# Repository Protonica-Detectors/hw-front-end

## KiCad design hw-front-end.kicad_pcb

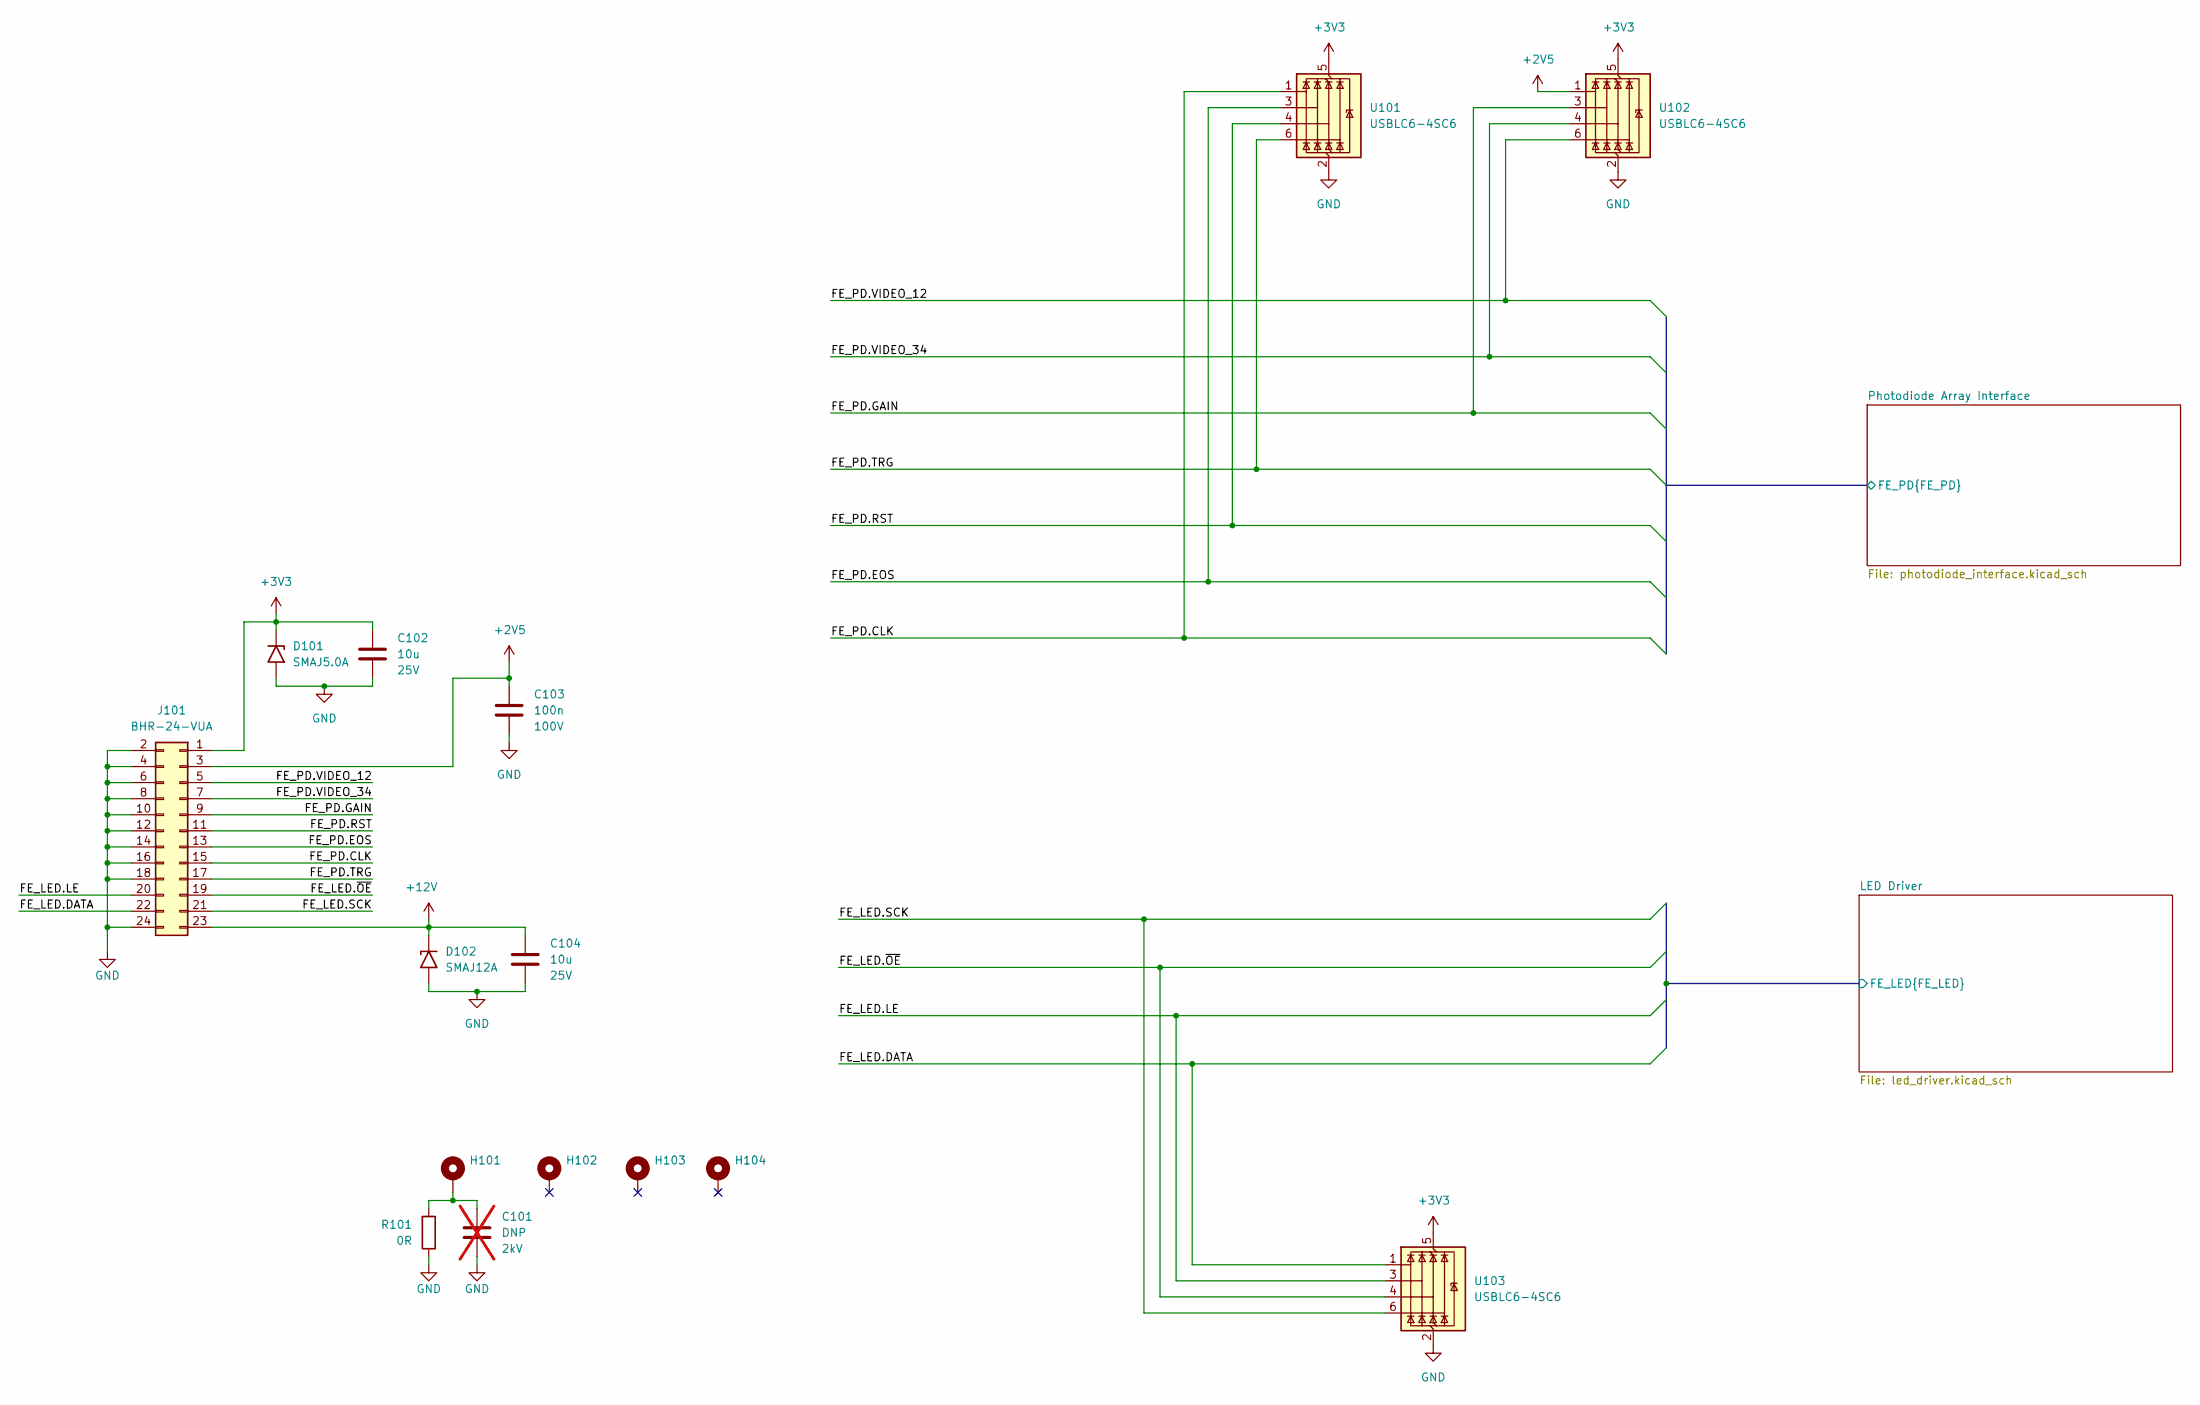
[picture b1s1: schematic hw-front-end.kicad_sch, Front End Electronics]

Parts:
C101: DNP; C_1206_3216Metric_Pad1.33x1.80mm_HandSolder; Voltage 2kV; not fitted
C102, C104: 10u; C_1206_3216Metric_Pad1.33x1.80mm_HandSolder; Voltage 25V; MPN GRM31CR71E106KA12L
C103: 100n; C_0805_2012Metric_Pad1.18x1.45mm_HandSolder; Voltage 100V; MPN GCM21BR72A104KA37L
D101: SMAJ5.0A; D_SMA; MPN SMAJ5.0A
D102: SMAJ12A; D_SMA; MPN SMAJ12A
H101, H102, H103, H104: MountingHole_Pad; MountingHole_3.2mm_M3_DIN965_Pad_TopBottom
J101: BHR-24-VUA; IDC-Header_2x12_P2.54mm_Vertical; MPN BHR-24-VUA
R101: 0R; R_0805_2012Metric_Pad1.20x1.40mm_HandSolder; MPN CRCW08050000Z0EA
U101, U102, U103: USBLC6-4SC6; SOT-23-6; MPN USBLC6-4SC6

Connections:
+2V5: C103.1, J101.3, U102.1 (I/O1); also elsewhere on the board
+3V3: C102.1, D101.1 (A1), J101.1, U101.5 (VBUS), U102.5 (VBUS), U103.5 (VBUS); also elsewhere on the board
+12V: C104.1, D102.1 (A1), J101.23; also elsewhere on the board
/LED Driver/FE_LED.DATA: J101.22, U103.1 (I/O1); also elsewhere on the board
/LED Driver/FE_LED.LE: J101.20, U103.3 (I/O2); also elsewhere on the board
/LED Driver/FE_LED.SCK: J101.21, U103.6 (I/O4); also elsewhere on the board
/LED Driver/FE_LED.~OE: J101.19, U103.4 (I/O3); also elsewhere on the board
/Photodiode Array Interface/FE_PD.CLK: J101.15, U101.1 (I/O1); also elsewhere on the board
/Photodiode Array Interface/FE_PD.EOS: J101.13, U101.3 (I/O2); also elsewhere on the board
/Photodiode Array Interface/FE_PD.GAIN: J101.9, U102.3 (I/O2); also elsewhere on the board
/Photodiode Array Interface/FE_PD.RST: J101.11, U101.4 (I/O3); also elsewhere on the board
/Photodiode Array Interface/FE_PD.TRG: J101.17, U101.6 (I/O4); also elsewhere on the board
/Photodiode Array Interface/FE_PD.VIDEO_12: J101.5, U102.6 (I/O4); also elsewhere on the board
/Photodiode Array Interface/FE_PD.VIDEO_34: J101.7, U102.4 (I/O3); also elsewhere on the board
GND: C101.2, C102.2, C103.2, C104.2, D101.2 (A2), D102.2 (A2), J101.2, J101.4, J101.6, J101.8, J101.10, J101.12, J101.14, J101.16, J101.18, J101.24, R101.1, U101.2 (GND), U102.2 (GND), U103.2 (GND); also elsewhere on the board
unnamed: C101.1, H101.1 (1_1), R101.2

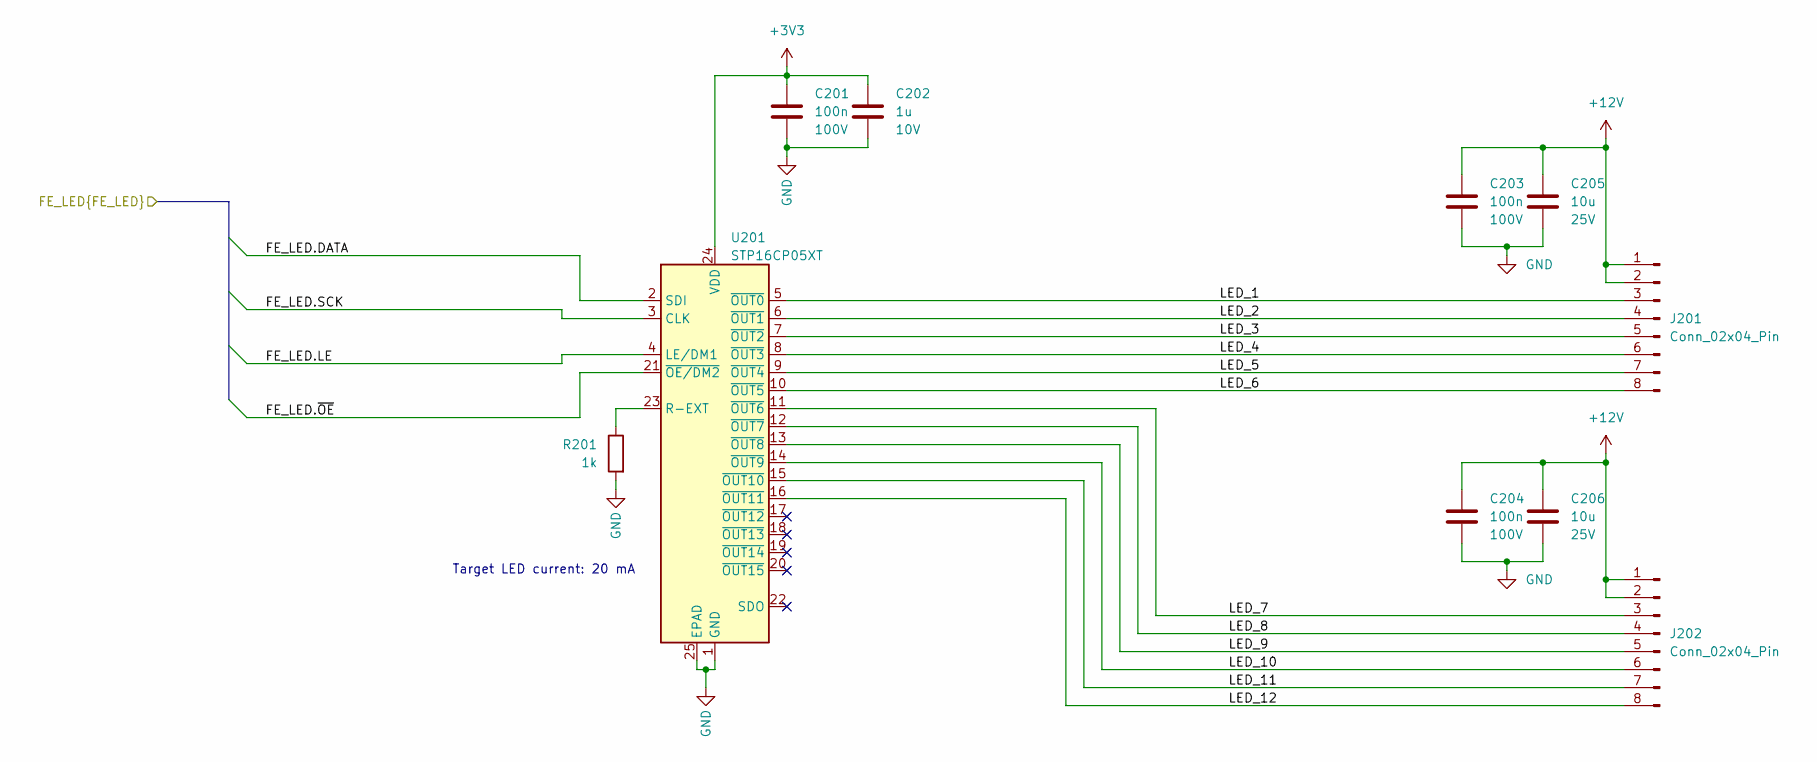
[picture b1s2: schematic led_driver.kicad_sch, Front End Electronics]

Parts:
C201, C203, C204: 100n; C_0805_2012Metric_Pad1.18x1.45mm_HandSolder; Voltage 100V; MPN GCM21BR72A104KA37L
C202: 1u; C_0805_2012Metric_Pad1.18x1.45mm_HandSolder; Voltage 10V; MPN GRM21BR71A105KA01L
C205, C206: 10u; C_1206_3216Metric_Pad1.33x1.80mm_HandSolder; Voltage 25V; MPN GRM31CR71E106KA12L
J201, J202: Conn_02x04_Pin; IDC-Header_2x04_P2.54mm_Vertical; MPN BHR-08-VUA
R201: 1k; R_0805_2012Metric_Pad1.20x1.40mm_HandSolder; MPN CRCW08051K00FKEA
U201: STP16CP05XT; HTSSOP-24-1EP_4.4x7.8mm_P0.65mm_EP3.2x5mm; MPN STP16CP05XTTR

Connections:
+3V3: C201.1, C202.1, U201.24 (VDD); also elsewhere on the board
+12V: C203.1, C204.1, C205.1, C206.1, J201.1, J201.2, J202.1, J202.2; also elsewhere on the board
/LED Driver/FE_LED.DATA: U201.2 (SDI); also elsewhere on the board
/LED Driver/FE_LED.LE: U201.4 (LE/DM1); also elsewhere on the board
/LED Driver/FE_LED.SCK: U201.3 (CLK); also elsewhere on the board
/LED Driver/FE_LED.~OE: U201.21 (~OE/DM2); also elsewhere on the board
/LED Driver/LED_1: J201.3, U201.5 (~OUT0)
/LED Driver/LED_2: J201.4, U201.6 (~OUT1)
/LED Driver/LED_3: J201.5, U201.7 (~OUT2)
/LED Driver/LED_4: J201.6, U201.8 (~OUT3)
/LED Driver/LED_5: J201.7, U201.9 (~OUT4)
/LED Driver/LED_6: J201.8, U201.10 (~OUT5)
/LED Driver/LED_7: J202.3, U201.11 (~OUT6)
/LED Driver/LED_8: J202.4, U201.12 (~OUT7)
/LED Driver/LED_9: J202.5, U201.13 (~OUT8)
/LED Driver/LED_10: J202.6, U201.14 (~OUT9)
/LED Driver/LED_11: J202.7, U201.15 (~OUT10)
/LED Driver/LED_12: J202.8, U201.16 (~OUT11)
GND: C201.2, C202.2, C203.2, C204.2, C205.2, C206.2, R201.2, U201.1 (GND), U201.25 (EPAD); also elsewhere on the board
unnamed: R201.1, U201.23 (R-EXT)

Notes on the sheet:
Target LED current: 20 mA

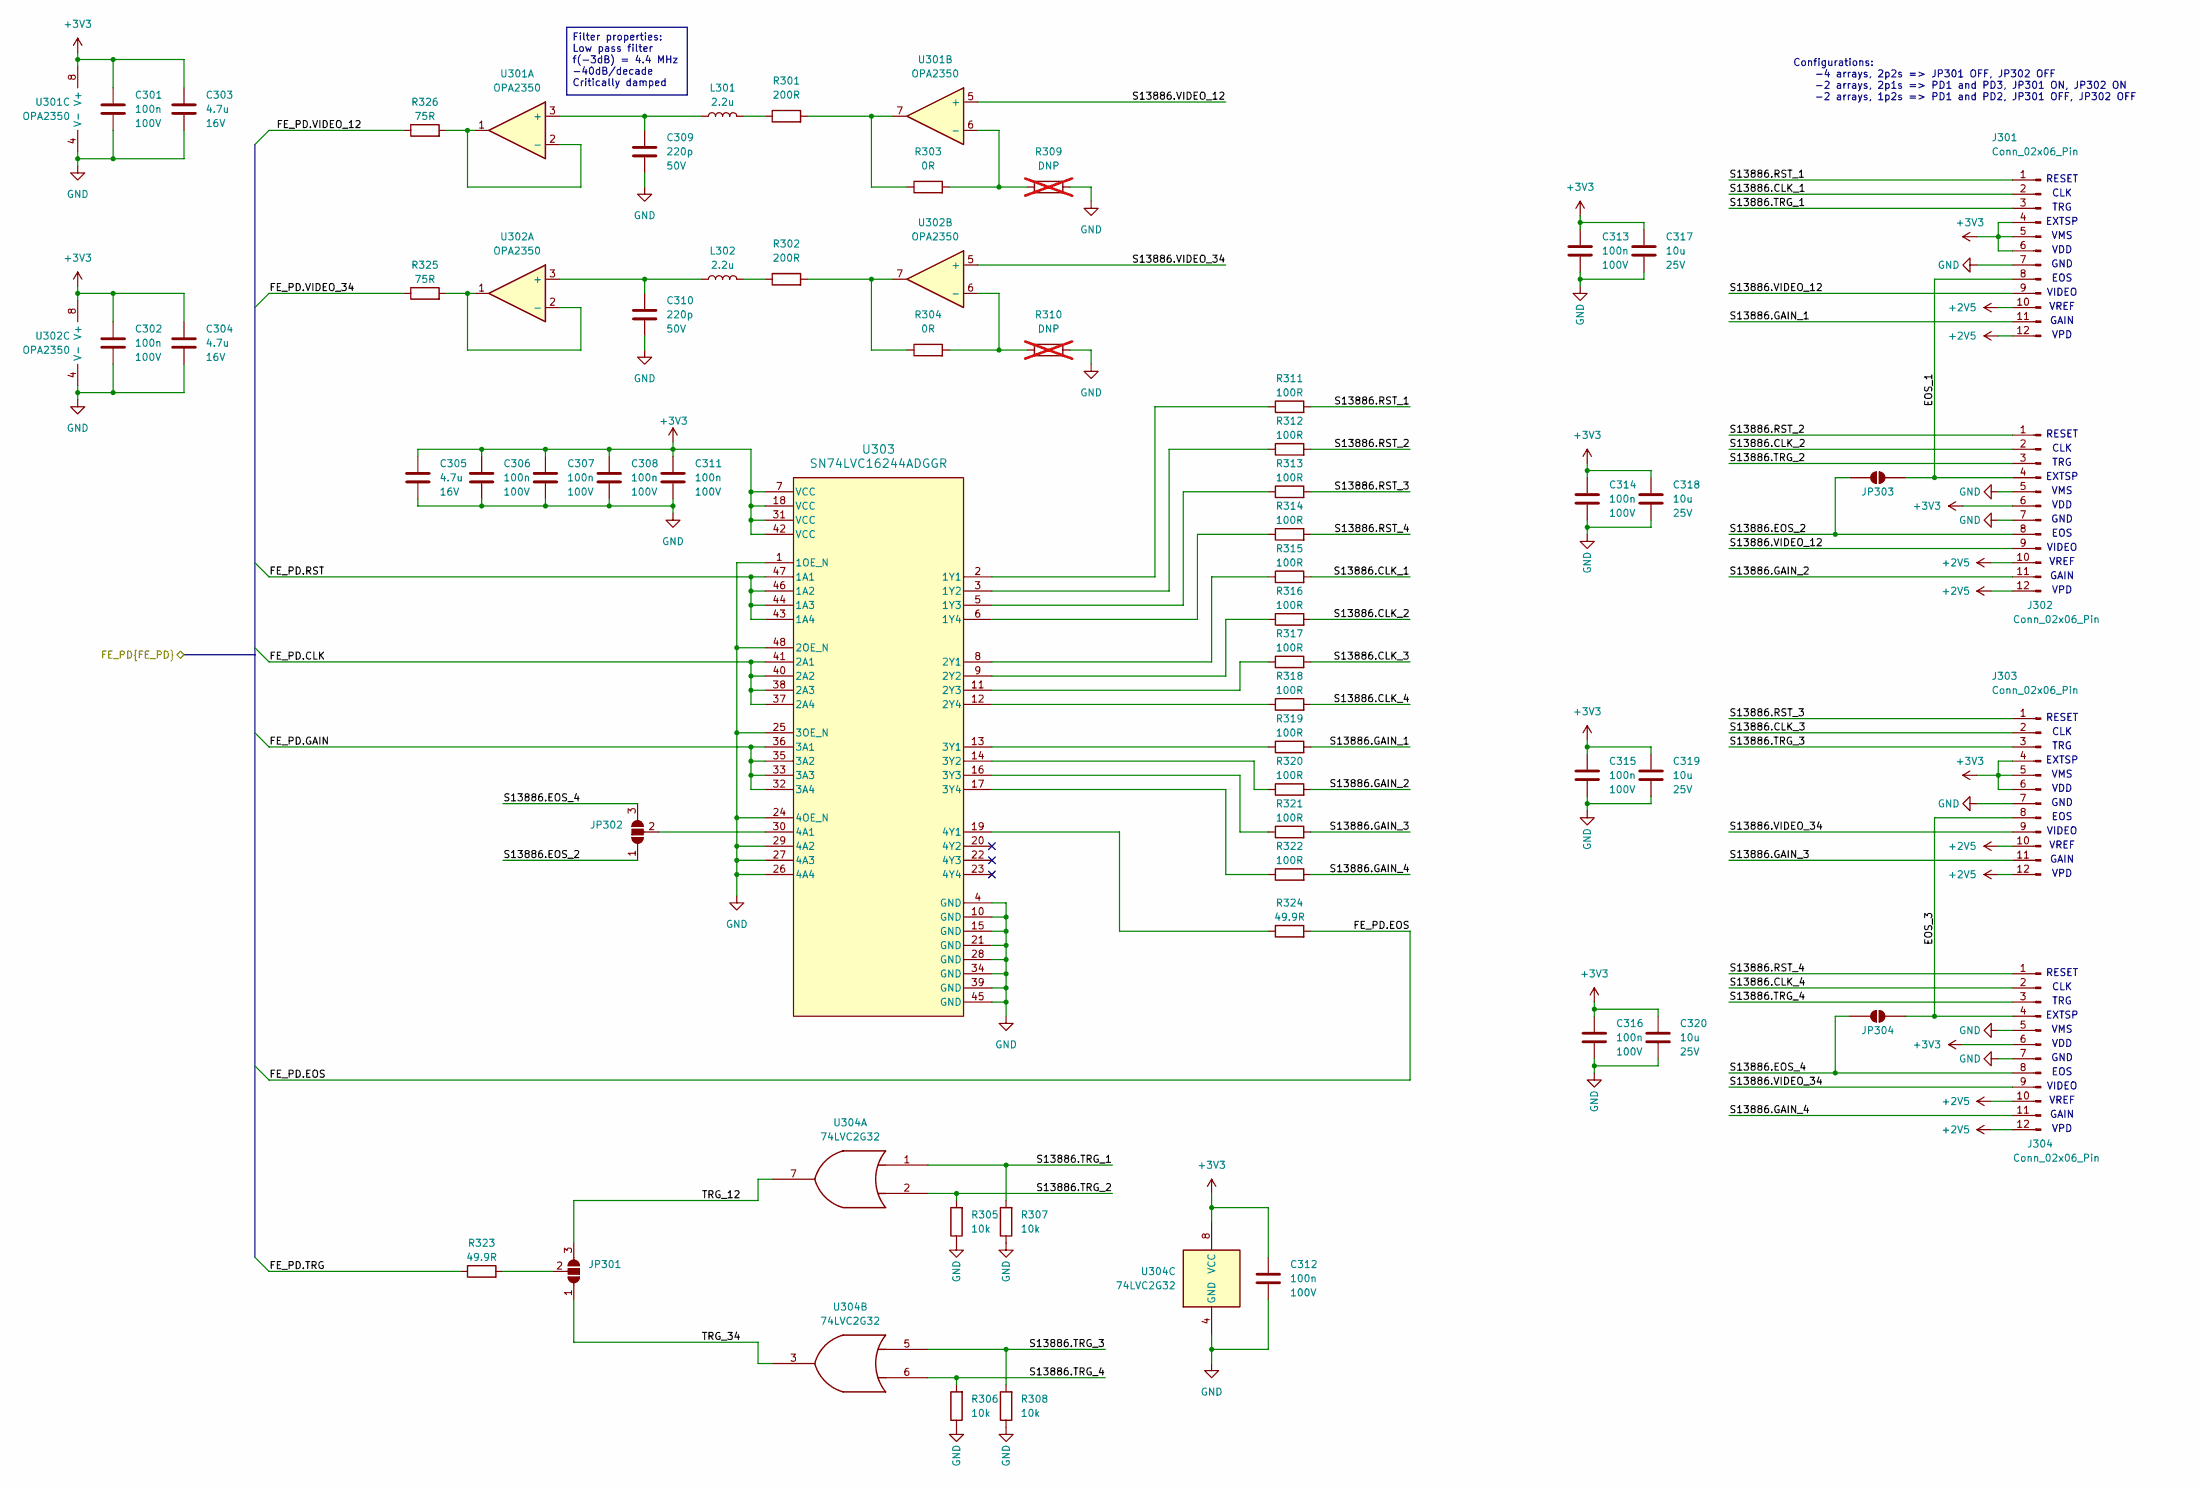
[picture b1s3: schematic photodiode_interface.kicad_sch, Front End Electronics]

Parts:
C301, C302, C306, C307, C308, C311, C312, C313, C314, C315, C316: 100n; C_0805_2012Metric_Pad1.18x1.45mm_HandSolder; Voltage 100V; MPN GCM21BR72A104KA37L
C303, C304, C305: 4.7u; C_0805_2012Metric_Pad1.18x1.45mm_HandSolder; Voltage 16V; MPN GRM21BR71C475KE51L
C309, C310: 220p; C_0805_2012Metric_Pad1.18x1.45mm_HandSolder; Voltage 50V; MPN C0805C221J5RACTU
C317, C318, C319, C320: 10u; C_1206_3216Metric_Pad1.33x1.80mm_HandSolder; Voltage 25V; MPN GRM31CR71E106KA12L
J301, J302, J303, J304: Conn_02x06_Pin; IDC-Header_2x06_P2.54mm_Vertical; MPN BHR-12-VUA
JP301, JP302: SolderJumper_3_Open; SolderJumper-3_P1.3mm_Open_Pad1.0x1.5mm
JP303, JP304: SolderJumper_2_Open; SolderJumper-2_P1.3mm_Open_Pad1.0x1.5mm
L301, L302: 2.2u; L_0805_2012Metric; MPN 74479052
R301, R302: 200R; R_0805_2012Metric_Pad1.20x1.40mm_HandSolder; MPN CRCW0805200RFKEA
R303, R304: 0R; R_0805_2012Metric_Pad1.20x1.40mm_HandSolder; MPN CRCW08050000Z0EA
R305, R306, R307, R308: 10k; R_0805_2012Metric_Pad1.20x1.40mm_HandSolder; MPN CRCW080510K0FKEA
R309, R310: DNP; R_0805_2012Metric_Pad1.20x1.40mm_HandSolder; not fitted
R311, R312, R313, R314, R315, R316, R317, R318, R319, R320, R321, R322: 100R; R_0805_2012Metric_Pad1.20x1.40mm_HandSolder; MPN CRCW0805100RFKEA
R323, R324: 49.9R; R_0805_2012Metric_Pad1.20x1.40mm_HandSolder; MPN CRCW080549R9FKEA
R325, R326: 75R; R_0805_2012Metric_Pad1.20x1.40mm_HandSolder; MPN CRCW080575R0FKEA
U301, U302: OPA2350; SOIC-8_3.9x4.9mm_P1.27mm; MPN OPA2350UA/2K5
U303: SN74LVC16244ADGGR; TSSOP-48_6.1x12.5mm_P0.5mm; MPN SN74LVC16244ADGGR
U304: 74LVC2G32; VSSOP-8_3x3mm_P0.65mm; MPN SN74LVC2G32DCTR

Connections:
+2V5: J301.10, J301.12, J302.10, J302.12, J303.10, J303.12, J304.10, J304.12; also elsewhere on the board
+3V3: C301.1, C302.1, C303.1, C304.1, C305.1, C306.1, C307.1, C308.1, C311.1, C312.1, C313.1, C314.1, C315.1, C316.1, C317.1, C318.1, C319.1, C320.1, J301.4, J301.5, J301.6, J302.6, J303.4, J303.5, J303.6, J304.6, U301.8 (V+), U302.8 (V+), U303.7 (VCC), U303.18 (VCC), U303.31 (VCC), U303.42 (VCC), U304.8 (VCC); also elsewhere on the board
/Photodiode Array Interface/EOS_1: J301.8, J302.4, JP303.1 (A)
/Photodiode Array Interface/EOS_3: J303.8, J304.4, JP304.1 (A)
/Photodiode Array Interface/FE_PD.CLK: U303.37 (2A4), U303.38 (2A3), U303.40 (2A2), U303.41 (2A1); also elsewhere on the board
/Photodiode Array Interface/FE_PD.EOS: R324.2; also elsewhere on the board
/Photodiode Array Interface/FE_PD.GAIN: U303.32 (3A4), U303.33 (3A3), U303.35 (3A2), U303.36 (3A1); also elsewhere on the board
/Photodiode Array Interface/FE_PD.RST: U303.43 (1A4), U303.44 (1A3), U303.46 (1A2), U303.47 (1A1); also elsewhere on the board
/Photodiode Array Interface/FE_PD.TRG: R323.1; also elsewhere on the board
/Photodiode Array Interface/FE_PD.VIDEO_12: R326.1; also elsewhere on the board
/Photodiode Array Interface/FE_PD.VIDEO_34: R325.1; also elsewhere on the board
/Photodiode Array Interface/S13886.CLK_1: J301.2, R315.2
/Photodiode Array Interface/S13886.CLK_2: J302.2, R316.2
/Photodiode Array Interface/S13886.CLK_3: J303.2, R317.2
/Photodiode Array Interface/S13886.CLK_4: J304.2, R318.2
/Photodiode Array Interface/S13886.EOS_2: J302.8, JP302.1 (A), JP303.2 (B)
/Photodiode Array Interface/S13886.EOS_4: J304.8, JP302.3 (B), JP304.2 (B)
/Photodiode Array Interface/S13886.GAIN_1: J301.11, R319.2
/Photodiode Array Interface/S13886.GAIN_2: J302.11, R320.2
/Photodiode Array Interface/S13886.GAIN_3: J303.11, R321.2
/Photodiode Array Interface/S13886.GAIN_4: J304.11, R322.2
/Photodiode Array Interface/S13886.RST_1: J301.1, R311.2
/Photodiode Array Interface/S13886.RST_2: J302.1, R312.2
/Photodiode Array Interface/S13886.RST_3: J303.1, R313.2
/Photodiode Array Interface/S13886.RST_4: J304.1, R314.2
/Photodiode Array Interface/S13886.TRG_1: J301.3, R307.2, U304.1
/Photodiode Array Interface/S13886.TRG_2: J302.3, R305.2, U304.2
/Photodiode Array Interface/S13886.TRG_3: J303.3, R308.2, U304.5
/Photodiode Array Interface/S13886.TRG_4: J304.3, R306.2, U304.6
/Photodiode Array Interface/S13886.VIDEO_12: J301.9, J302.9, U301.5 (+)
/Photodiode Array Interface/S13886.VIDEO_34: J303.9, J304.9, U302.5 (+)
/Photodiode Array Interface/TRG_12: JP301.3 (B), U304.7
/Photodiode Array Interface/TRG_34: JP301.1 (A), U304.3
GND: C301.2, C302.2, C303.2, C304.2, C305.2, C306.2, C307.2, C308.2, C309.2, C310.2, C311.2, C312.2, C313.2, C314.2, C315.2, C316.2, C317.2, C318.2, C319.2, C320.2, J301.7, J302.5, J302.7, J303.7, J304.5, J304.7, R305.1, R306.1, R307.1, R308.1, R309.2, R310.2, U301.4 (V-), U302.4 (V-), U303.1 (1OE_N), U303.4 (GND), U303.10 (GND), U303.15 (GND), U303.21 (GND), U303.24 (4OE_N), U303.25 (3OE_N), U303.26 (4A4), U303.27 (4A3), U303.28 (GND), U303.29 (4A2), U303.34 (GND), U303.39 (GND), U303.45 (GND), U303.48 (2OE_N), U304.4 (GND); also elsewhere on the board
unnamed: JP301.2 (C), R323.2
unnamed: JP302.2 (C), U303.30 (4A1)
unnamed: L301.2, R301.1
unnamed: L302.2, R302.1
unnamed: R301.2, R303.1, U301.7
unnamed: R302.2, R304.1, U302.7
unnamed: C309.1, L301.1, U301.3 (+)
unnamed: R326.2, U301.1, U301.2 (-)
unnamed: R303.2, R309.1, U301.6 (-)
unnamed: C310.1, L302.1, U302.3 (+)
unnamed: R325.2, U302.1, U302.2 (-)
unnamed: R304.2, R310.1, U302.6 (-)
unnamed: R311.1, U303.2 (1Y1)
unnamed: R312.1, U303.3 (1Y2)
unnamed: R313.1, U303.5 (1Y3)
unnamed: R314.1, U303.6 (1Y4)
unnamed: R315.1, U303.8 (2Y1)
unnamed: R316.1, U303.9 (2Y2)
unnamed: R317.1, U303.11 (2Y3)
unnamed: R318.1, U303.12 (2Y4)
unnamed: R319.1, U303.13 (3Y1)
unnamed: R320.1, U303.14 (3Y2)
unnamed: R321.1, U303.16 (3Y3)
unnamed: R322.1, U303.17 (3Y4)
unnamed: R324.1, U303.19 (4Y1)

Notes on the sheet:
EXTSP
Configurations: -4 arrays, 2p2s => JP301 OFF, JP302 OFF -2 arrays, 2p1s => PD1 and PD3, JP301 ON, JP302 ON -2 arrays, 1p2s => PD1 and PD2, JP301 OFF, JP302 OFF
GND
TRG
VPD
VDD
VIDEO
CLK
EOS
GAIN
RESET
VMS
VREF
Filter properties: Low pass filter f(-3dB) = 4.4 MHz -40dB/decade Critically damped

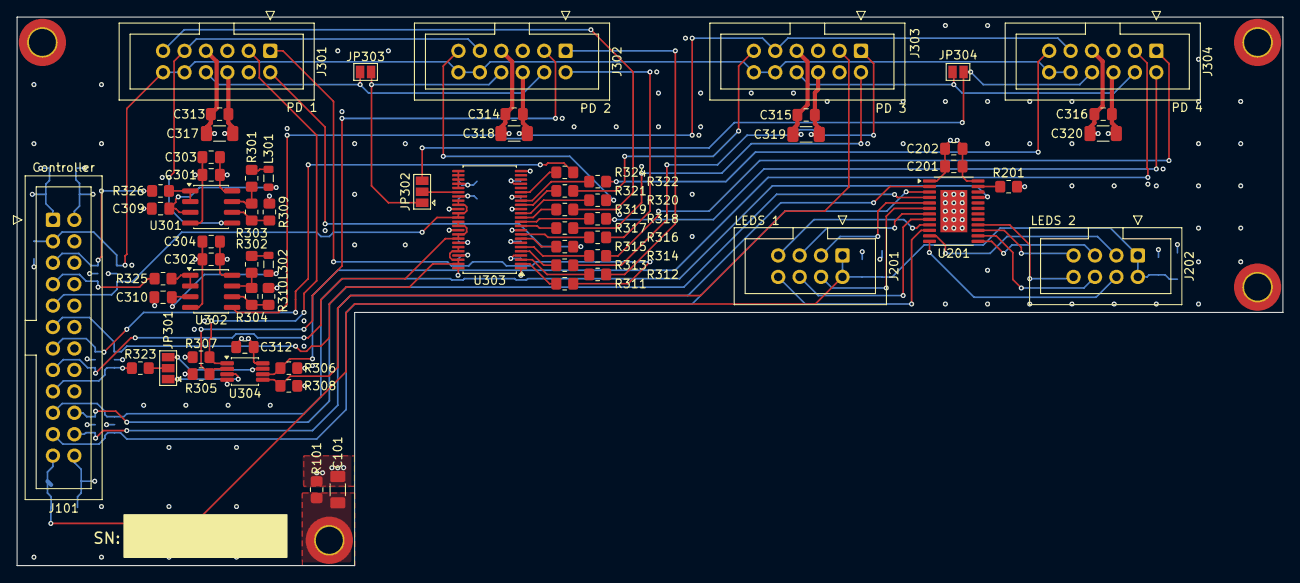
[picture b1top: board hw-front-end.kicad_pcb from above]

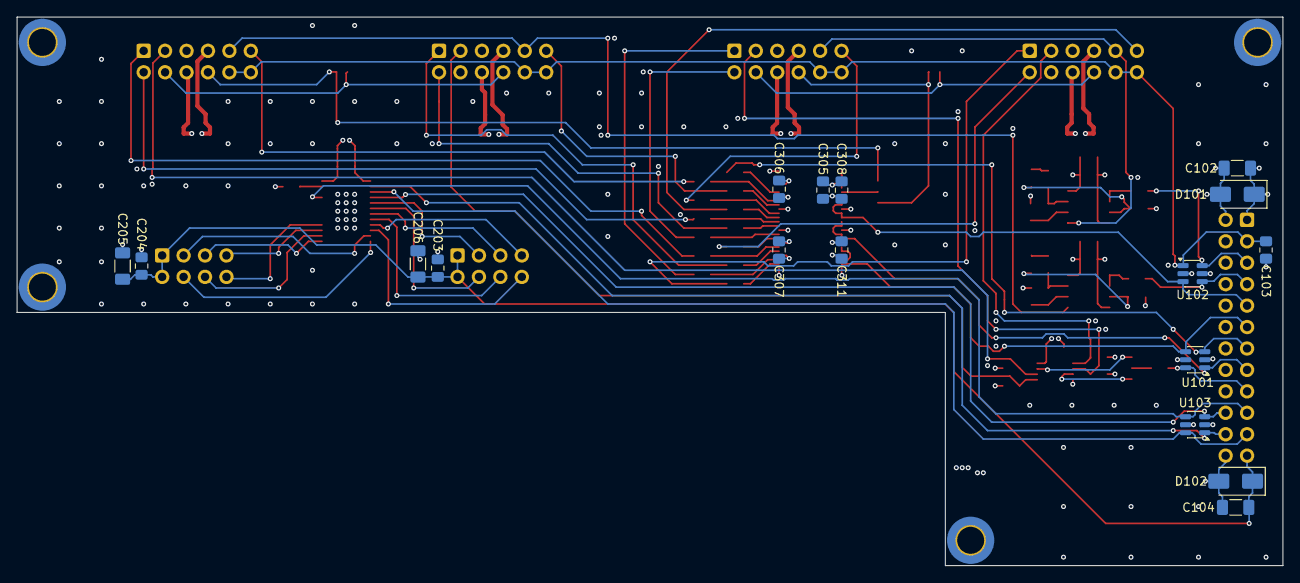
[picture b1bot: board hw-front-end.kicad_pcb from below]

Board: 6 copper layers, 150.0 x 65.0 mm, 85 parts (17 on the bottom side), 78 nets.

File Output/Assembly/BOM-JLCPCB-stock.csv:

Comment,Designator,Footprint,LCSC Part #
10u GRM31CR71E106KA12L,"C102,C104,C205,C206,C317,C318,C319,C320",1206,C77093
100n GCM21BR72A104KA37L,"C103,C201,C203,C204,C301,C302,C306,C307,C308,C311,C312,C313,C314,C315,C316",0805,C85866
1u GRM21BR71H105KA12L,C202,0805,C77083
4.7u GRM21BR71C475KE51L,"C303,C304,C305",0805,C408144
220p 0805CG221J500NT,"C309,C310",0805,C1805
SMAJ5.0A SMAJ5.0A,D101,DO-214AC(SMA),C83329
SMAJ12A SMAJ12A,D102,DO-214AC(SMA),C148213
2.2u MLF2012A2R2KT000,"L301,L302",0805,C136256
0R CRCW08050000Z0EA,"R101,R303,R304",0805,C844934
1k CRCW08051K00FKEA,R201,0805,C844939
200R CRCW0805200RFKEA,"R301,R302",0805,C844828
10k CRCW080510K0FKEA,"R305,R306,R307,R308",0805,C844937
100R CRCW0805100RFKEA,"R311,R312,R313,R314,R315,R316,R317,R318,R319,R320,R321,R322",0805,C844936
49.9R CRCW080549R9FKEA,"R323,R324",0805,C844847
75R CRCW080575R0FKEA,"R325,R326",0805,C844859
USBLC6-4SC6 USBLC6-4SC6,"U101,U102,U103",SOT-23-6L,C111212
STP16CP05XT STP16CP05XTTR,U201,TSSOP-24-EP,C2969824
OPA2350 OPA2350UA/2K5,"U301,U302",SOIC-8,C55904
SN74LVC16244ADGGR SN74LVC16244ADGGR,U303,TSSOP-48-6.1mm,C7822
74LVC2G32 SN74LVC2G32DCTR,U304,MSOP-8,C2862085
